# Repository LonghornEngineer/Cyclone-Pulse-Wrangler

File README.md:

Cyclone Pulse Wrangler
========

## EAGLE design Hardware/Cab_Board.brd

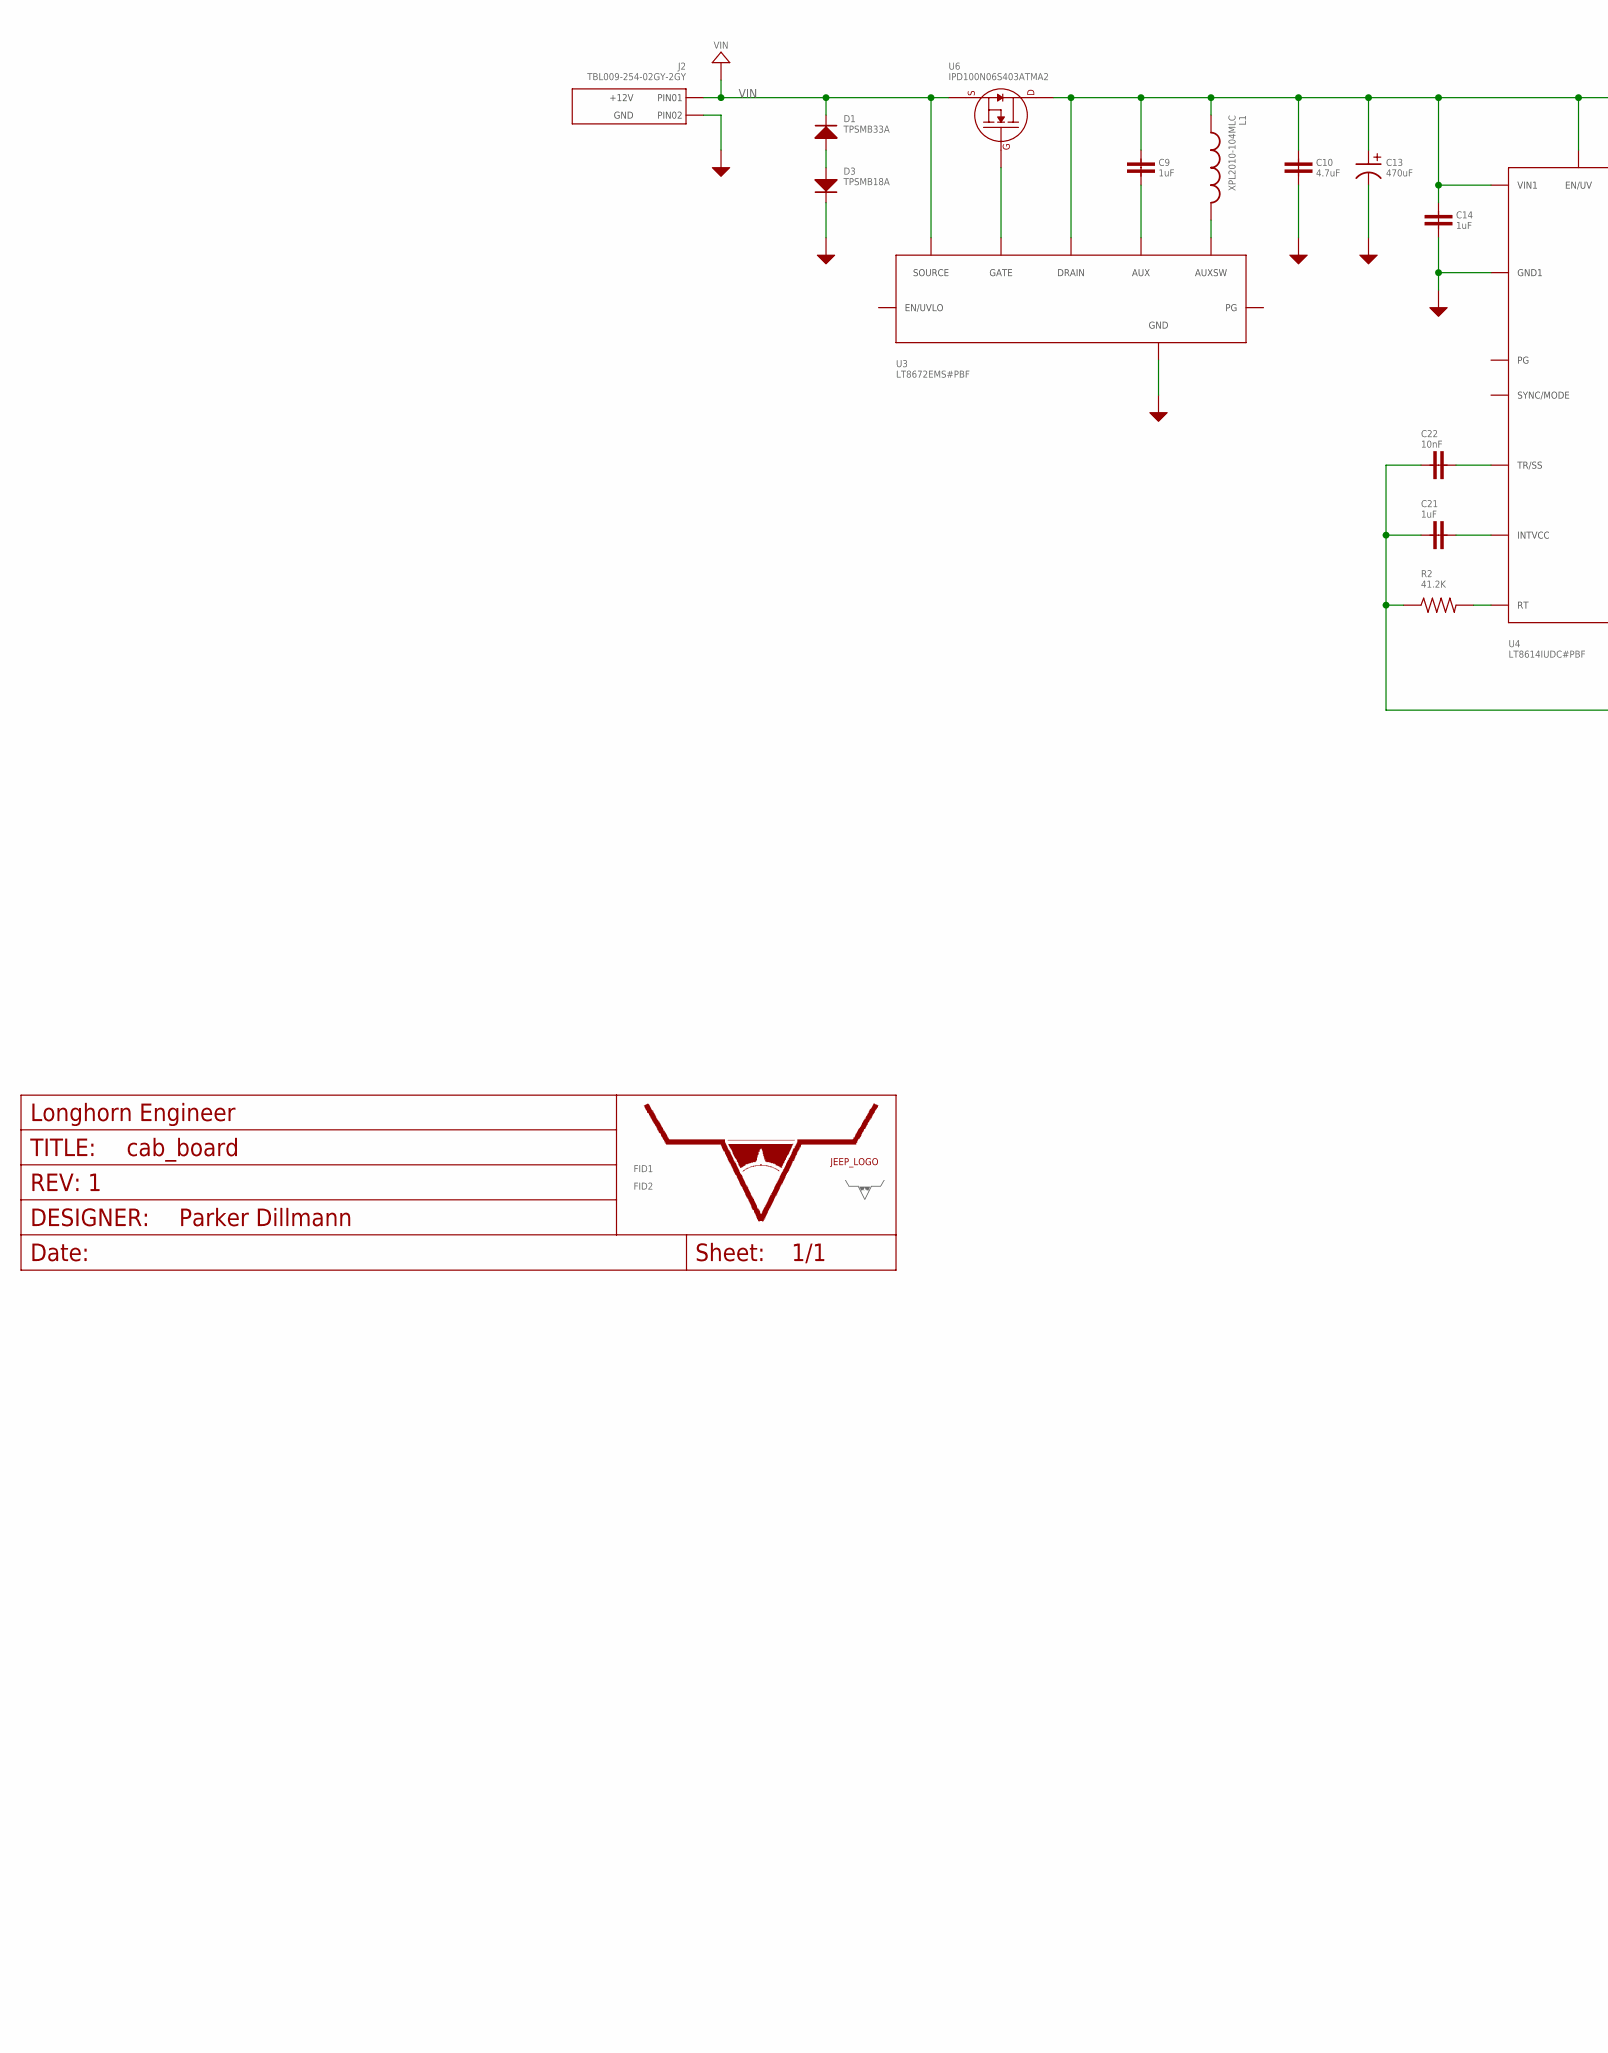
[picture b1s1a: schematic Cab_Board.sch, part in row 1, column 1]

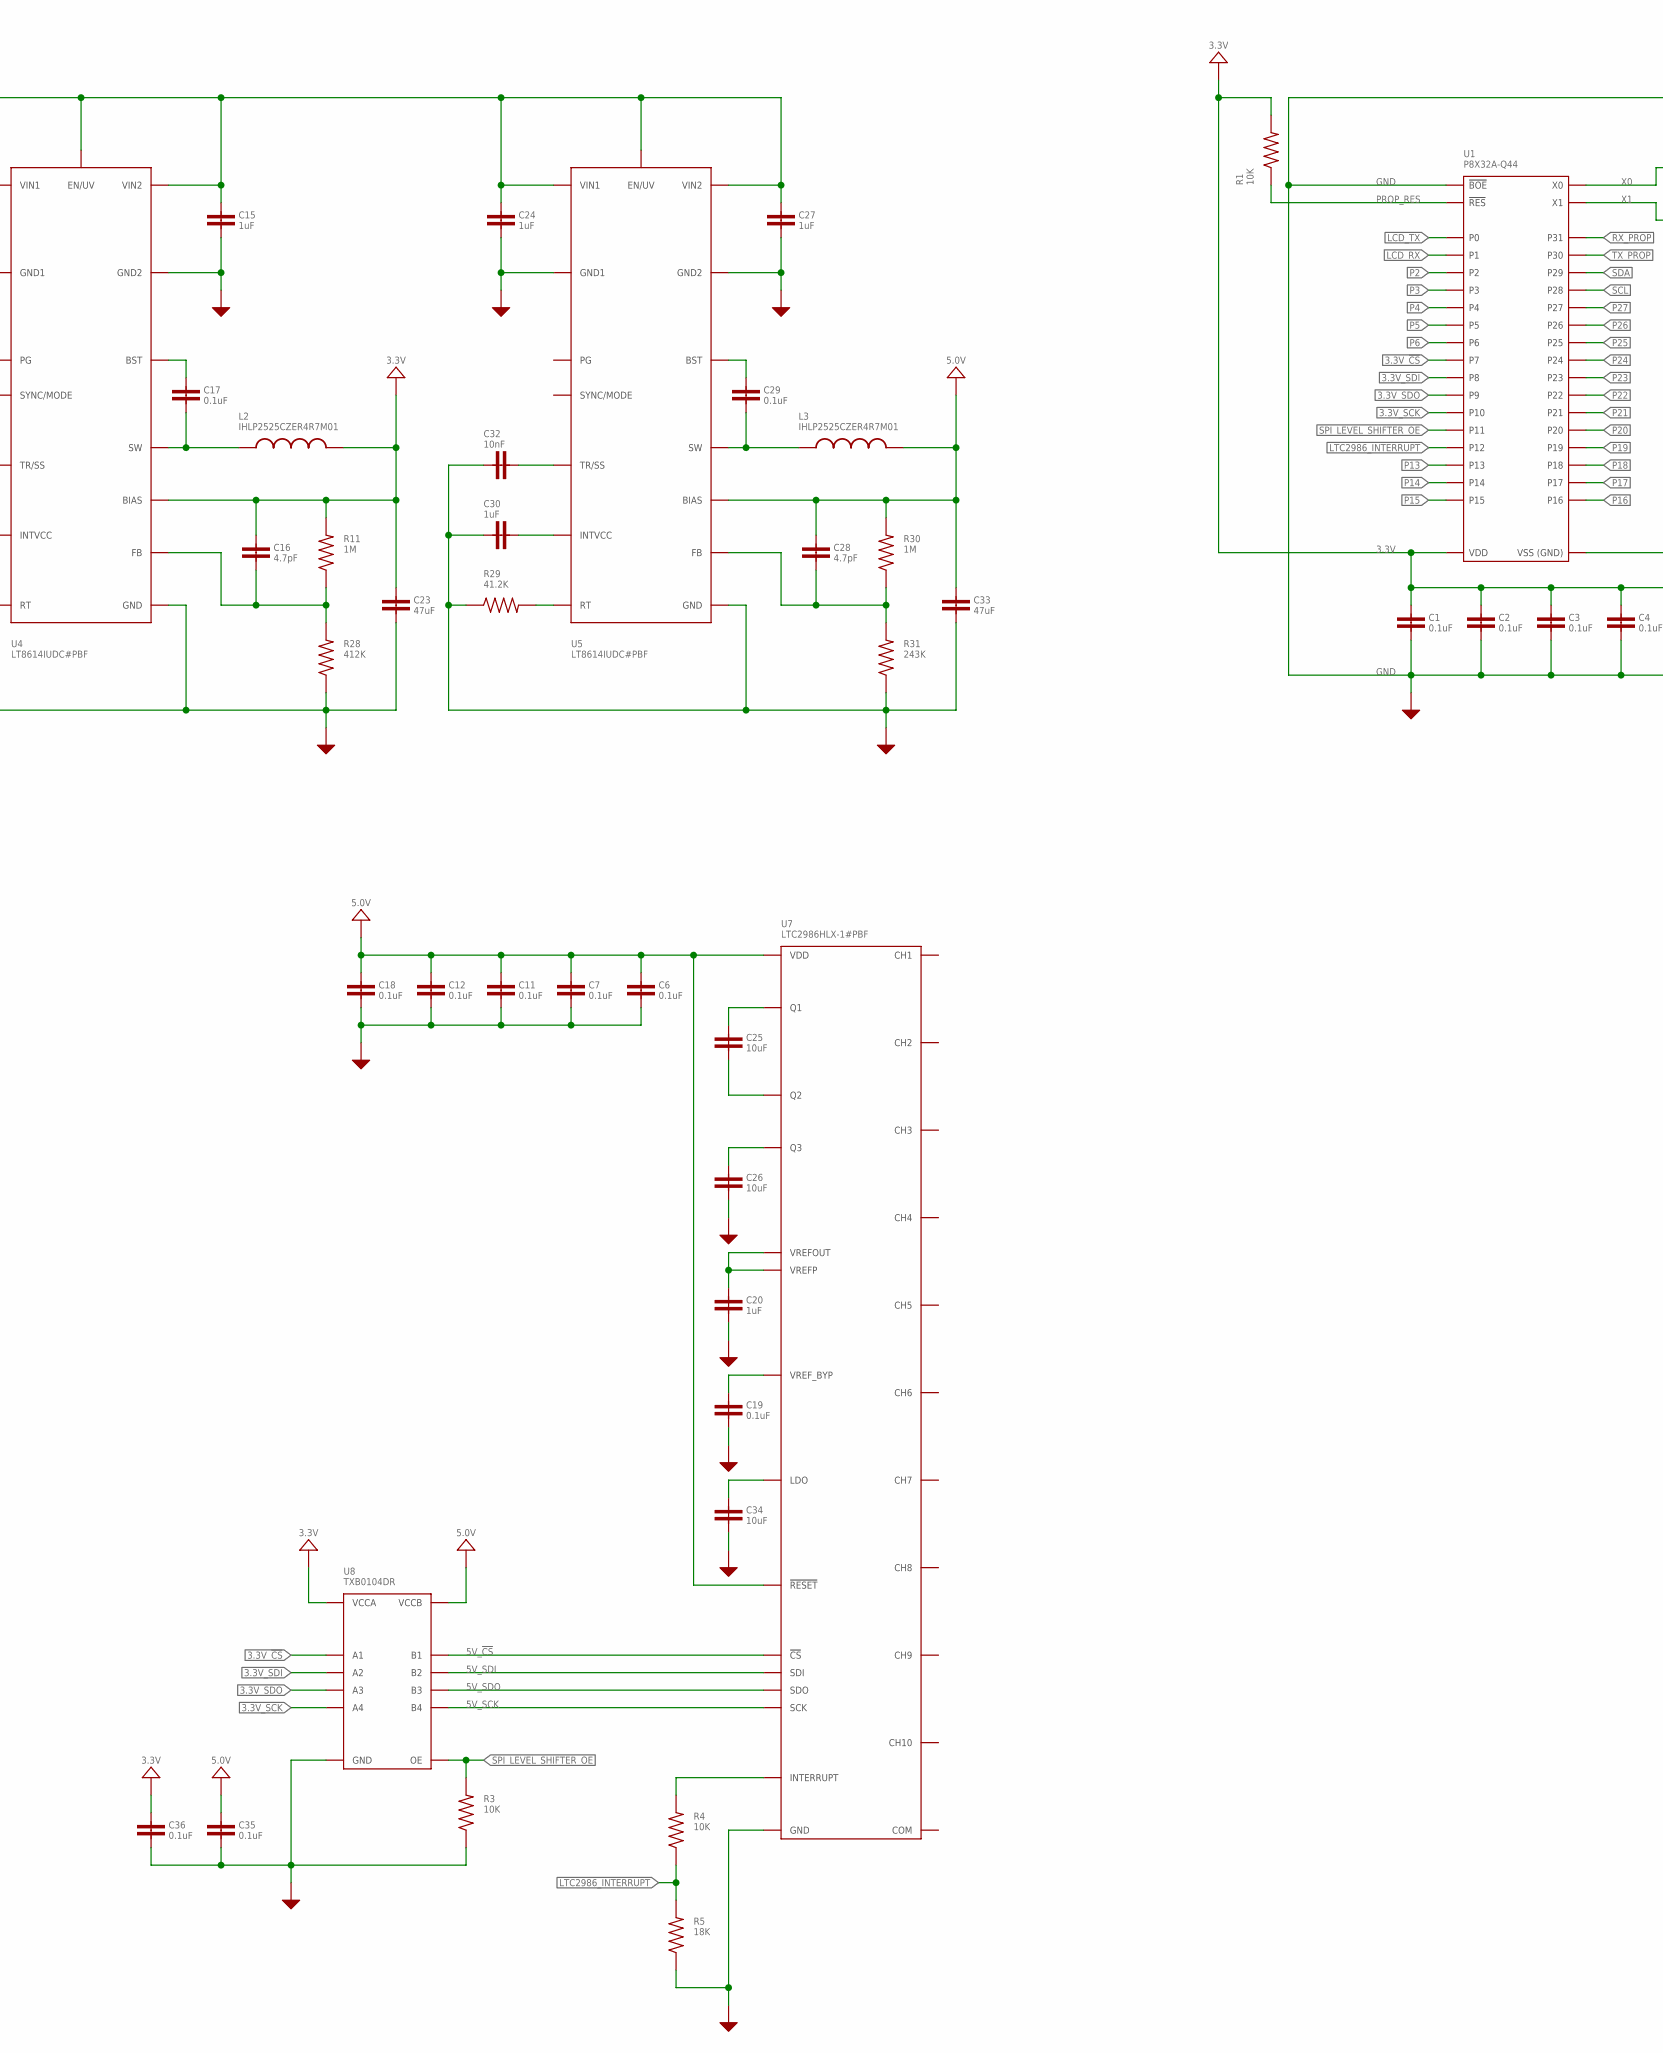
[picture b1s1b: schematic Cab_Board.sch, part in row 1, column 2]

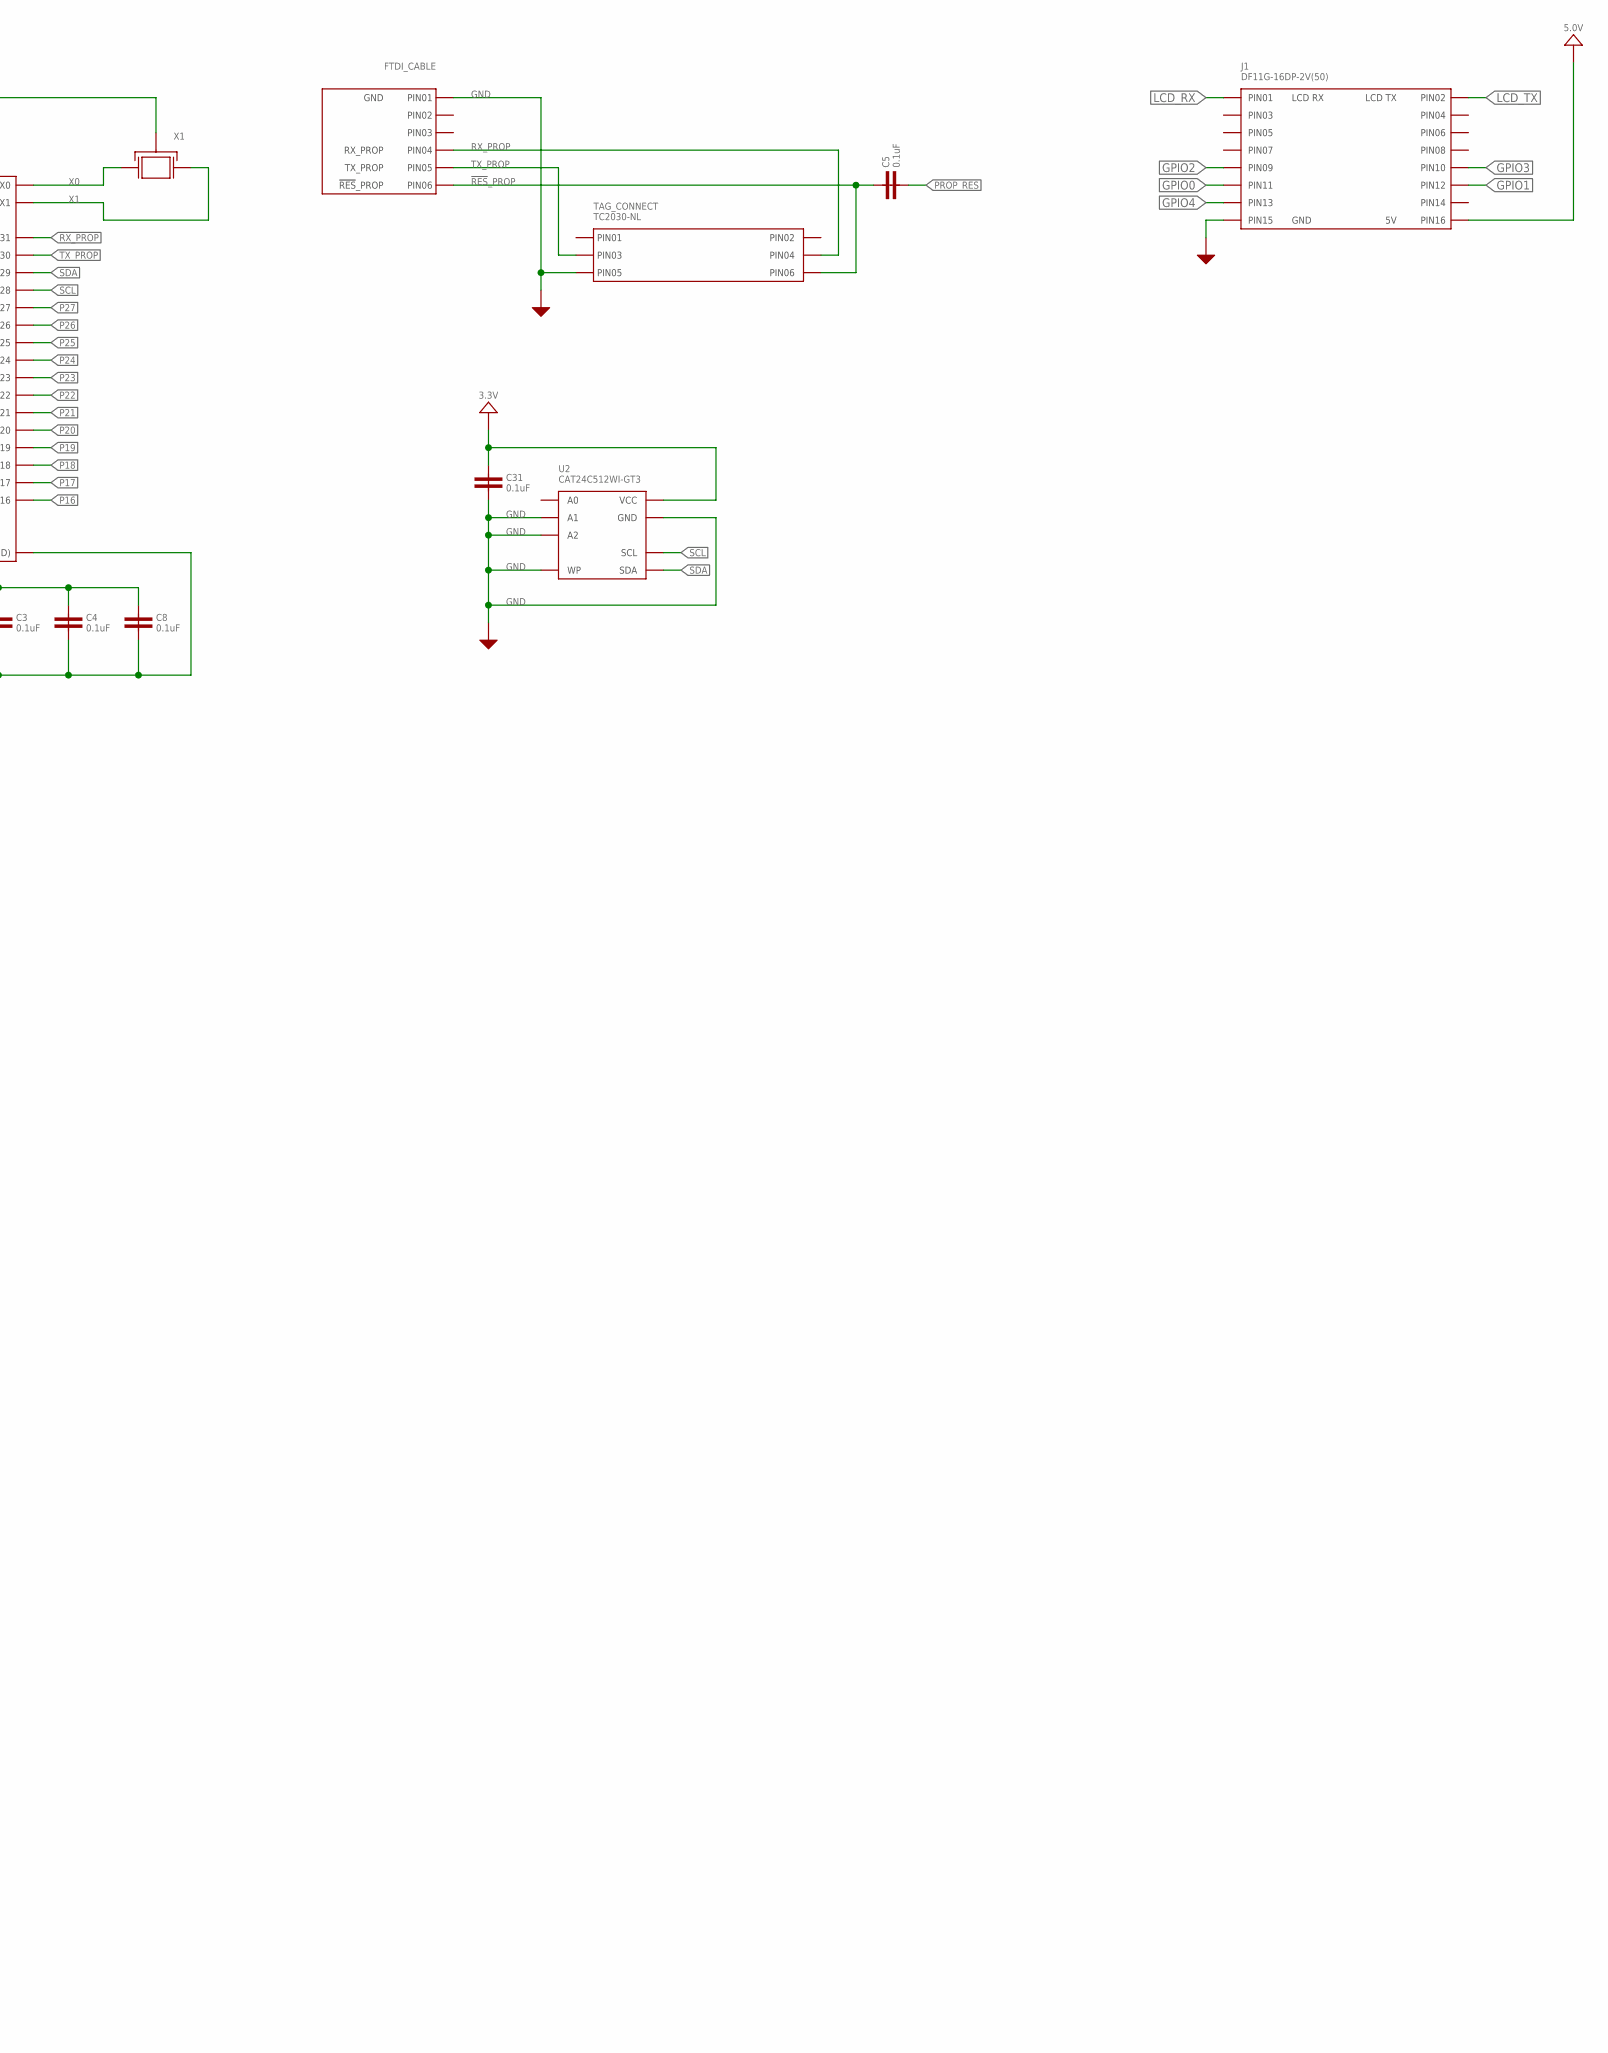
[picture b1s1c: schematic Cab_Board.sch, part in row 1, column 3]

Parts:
C1, C2, C3, C4, C6, C7, C8, C11, C12, C18, C19, C31, C35, C36: 0.1uF; 0805; MPN MF-CAP-0805-0.1uF
C5: 0.1uF; 0603; MPN MF-CAP-0805-0.1uF
C9, C14, C15, C21, C24, C27, C30: 1uF; 0805; MPN C0805X105K5RACAUTO
C10: 4.7uF; 1210; MPN UMJ325AB7475KMHP
C13: 470uF; 10MM_CAP_SMD; MPN EEH-ZS1V471P
C16, C28: 4.7pF; 0603; MPN C0603C479D5HACTU
C17, C29: 0.1uF; 0603; MPN MF-CAP-0603-0.1uF
C20: 1uF; 0805; MPN MF-CAP-0805-1uF
C22, C32: 10nF; 0603; MPN C0603X103K5RAC3316
C23, C33: 47uF; 1210; MPN GCJ32ER70J476KE01L
C25, C26, C34: 10uF; 1210; MPN CGA6P1X7R1N106K250AC
D1: TPSMB33A; DO-214AA; MPN TPSMB33A
D3: TPSMB18A; DO-214AA; MPN TPSMB18A
FID1, FID2: FIDUCIAL_0.5MM
FTDI_CABLE: CON_01X06_2.54MM_PIN_HEADER; 2.54MM_01X06_PIN_HEADER
J1: DF11G-16DP-2V(50); MPN DF11G-16DP-2V(50)
J2: TBL009-254-02GY-2GY
L1: XPL2010-104MLC; XPL2010; MPN XPL2010-104MLC
L2, L3: IHLP2525CZER4R7M01; IHLP-2525; MPN IHLP2525CZER4R7M01
R1: 10K; 0805
R2, R29: 41.2K; 0603
R3, R4: 10K; 0603; MPN MF-RES-0603-10K
R5: 18K; 0603
R11, R30: 1M; 0603
R28: 412K; 0603
R31: 243K; 0603
TAG_CONNECT: TC2030-NL; TC2030
U1: P8X32A-Q44; LQFP44
U2: CAT24C512WI-GT3; SOIC-8_W; MPN CAT24C512WI-GT3
U3: LT8672EMS#PBF; LT8672_MSOP-10; MPN LT8672EMS#PBF
U4, U5: LT8614IUDC#PBF; LT8614_QFN-18; MPN LT8614IUDC#PBF
U6: IPD100N06S403ATMA2; TO-252-3; MPN IPD100N06S403ATMA2
U7: LTC2986HLX-1#PBF; LQFP-48; MPN LTC2986HLX-1#PBF
U8: TXB0104DR; TXB0104_SOIC-14
U$1: LHE_FRAME
U$35: JEEP_LOGO_SILK_MEDIUM; JEEP_SILK_MEDIUM
U$42: LHE_LOGOLHE_LOGO; LHE_LOGO
X1: 6.0MHz; 7MMX5MM; MPN ABMM-6.000MHZ-B2-T

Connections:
3.3V: C1.1, C2.1, C3.1, C4.1, C8.1, C16.1, C23.1, C31.1, C36.1, L2.P$2, R1.2, R11.2, U1.8 (VDD), U1.18 (VDD), U1.30 (VDD), U1.40 (VDD), U2.8 (VCC), U4.1 (BIAS), U8.1 (VCCA)
3.3V_!CS: U1.4 (P7), U8.2 (A1)
3.3V_SCK: U1.11 (P10), U8.5 (A4)
3.3V_SDI: U1.9 (P8), U8.3 (A2)
3.3V_SDO: U1.10 (P9), U8.4 (A3)
5.0V: C6.1, C7.1, C11.1, C12.1, C18.1, C28.1, C33.1, C35.1, J1.P$16 (16), L3.P$2, R30.2, U5.1 (BIAS), U7.P$2 (VDD), U7.P$4 (VDD), U7.P$6 (VDD), U7.P$8 (VDD), U7.P$42 (!RESET), U7.P$45 (VDD), U8.14 (VCCB)
5V_!CS: U7.P$41 (!CS), U8.13 (B1)
5V_SCK: U7.P$38 (SCK), U8.10 (B4)
5V_SDI: U7.P$40 (SDI), U8.12 (B2)
5V_SDO: U7.P$39 (SDO), U8.11 (B3)
!RES!_PROP: C5.1, FTDI_CABLE.6, TAG_CONNECT.P$6 (PIN6)
BST: C17.1, U4.3 (BST)
BST1: C29.1, U5.3 (BST)
FB: C16.2, R11.1, R28.2, U4.20 (FB)
FB1: C28.2, R30.1, R31.2, U5.20 (FB)
GND: C1.2, C2.2, C3.2, C4.2, C6.2, C7.2, C8.2, C10.2, C11.2, C12.2, C13.NEG, C14.2, C15.2, C18.2, C19.2, C20.2, C21.1, C22.1, C23.2, C24.2, C26.2, C27.2, C30.1, C31.2, C32.1, C33.2, C34.2, C35.2, C36.2, D3.C (CATHODE), FTDI_CABLE.1, J1.P$15 (15), J2.2A (PIN2), J2.2B (PIN2), R2.1, R3.1, R5.1, R28.1, R29.1, R31.1, TAG_CONNECT.P$5 (PIN5), U1.5 (VSS), U1.6 (BOE'), U1.17 (VSS), U1.27 (VSS), U1.39 (VSS), U2.2 (A1), U2.3 (A2), U2.4 (GND), U2.7 (WP), U3.2 (GND), U3.4 (GND), U4.6 (GND1), U4.7 (GND1), U4.10 (GND2), U4.11 (GND2), U4.18 (GND), U5.6 (GND1), U5.7 (GND1), U5.10 (GND2), U5.11 (GND2), U5.18 (GND), U7.P$1 (GND), U7.P$3 (GND), U7.P$5 (GND), U7.P$7 (GND), U7.P$9 (GND), U7.P$12 (GND), U7.P$15 (GND), U7.P$26 (GND), U7.P$27 (GND), U7.P$28 (GND), U7.P$29 (GND), U7.P$30 (GND), U7.P$31 (GND), U7.P$32 (GND), U7.P$33 (GND), U7.P$34 (GND), U7.P$35 (GND), U7.P$44 (GND), U8.7 (GND), X1.P$2 (GND), X1.P$4 (GND)
GPIO0: J1.P$11 (11)
GPIO1: J1.P$12 (12)
GPIO2: J1.P$9 (9)
GPIO3: J1.P$10 (10)
GPIO4: J1.P$13 (13)
INTVCC: C21.2, U4.2 (INTVCC)
INTVCC1: C30.2, U5.2 (INTVCC)
LCD_RX: J1.P$1 (1), U1.42 (P1)
LCD_TX: J1.P$2 (2), U1.41 (P0)
LTC2986_INTERRUPT: R4.1, R5.2, U1.13 (P12)
unnamed: C19.1, U7.P$11 (VREF_BYP)
unnamed: U3.10 (GATE), U6.1 (GATE)
unnamed: C20.1, U7.P$13 (VREFOUT), U7.P$14 (VREFP)
unnamed: C26.1, U7.P$46 (Q3)
unnamed: C25.2, U7.P$47 (Q2)
unnamed: C25.1, U7.P$48 (Q1)
unnamed: C34.1, U7.P$43 (LDO)
unnamed: D1.A (ANODE), D3.A (ANODE)
unnamed: R4.2, U7.P$37 (INTERRUPT)
unnamed: C9.1, C10.1, C13.POS, C14.1, C15.1, C24.1, C27.1, L1.P$1, U3.8 (DRAIN), U4.4 (VIN1), U4.13 (VIN2), U4.14 (EN/UV), U5.4 (VIN1), U5.13 (VIN2), U5.14 (EN/UV), U6.PAD (DRAIN)
unnamed: C9.2, U3.7 (AUX)
unnamed: L1.P$2, U3.6 (AUXSW)
P2: U1.43 (P2)
P3: U1.44 (P3)
P4: U1.1 (P4)
P5: U1.2 (P5)
P6: U1.3 (P6)
P13: U1.14 (P13)
P14: U1.15 (P14)
P15: U1.16 (P15)
P16: U1.19 (P16)
P17: U1.20 (P17)
P18: U1.21 (P18)
P19: U1.22 (P19)
P20: U1.23 (P20)
P21: U1.24 (P21)
P22: U1.25 (P22)
P23: U1.26 (P23)
P24: U1.31 (P24)
P25: U1.32 (P25)
P26: U1.33 (P26)
P27: U1.34 (P27)
PROP_RES: C5.2, R1.1, U1.7 (RES')
RT: R2.2, U4.15 (RT)
RT1: R29.2, U5.15 (RT)
RX_PROP: FTDI_CABLE.4, TAG_CONNECT.P$4 (PIN4), U1.38 (P31)
SCL: U1.35 (P28), U2.6 (SCL)
SDA: U1.36 (P29), U2.5 (SDA)
SPI_LEVEL_SHIFTER_OE: R3.2, U1.12 (P11), U8.8 (OE)
SW: C17.2, L2.P$1, U4.8 (SW), U4.9 (SW), U4.21 (SW), U4.22 (SW)
SW1: C29.2, L3.P$1, U5.8 (SW), U5.9 (SW), U5.21 (SW), U5.22 (SW)
TR/SS: C22.2, U4.16 (TR/SS)
TR/SS1: C32.2, U5.16 (TR/SS)
TX_PROP: FTDI_CABLE.5, TAG_CONNECT.P$3 (PIN3), U1.37 (P30)
VIN: D1.C (CATHODE), J2.1A (PIN1), J2.1B (PIN1), U3.9 (SOURCE), U6.3 (SOURCE)
X0: U1.29 (X0), X1.P$3 (X1)
X1: U1.28 (X1), X1.P$1 (X0)

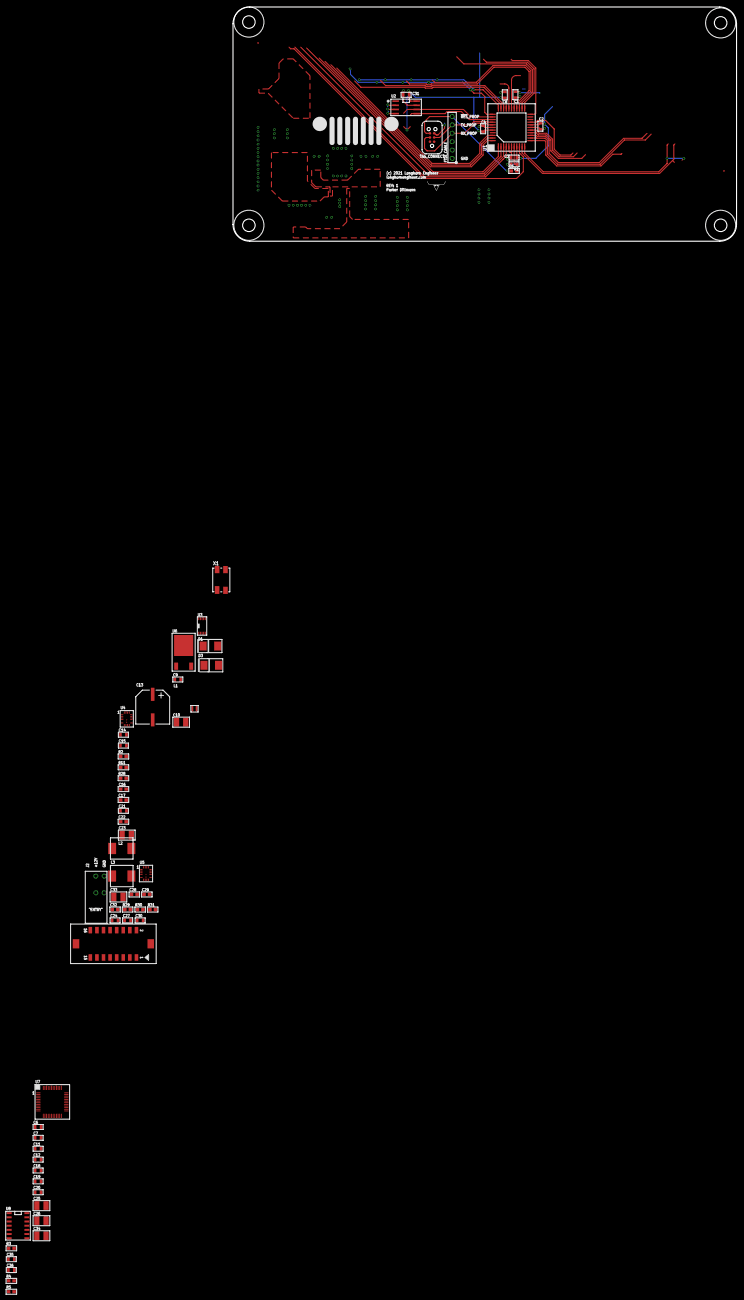
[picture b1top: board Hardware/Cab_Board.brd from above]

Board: 2 copper layers, 152.9 x 71.1 mm, 73 parts (0 on the bottom side), 48 nets.

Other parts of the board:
U$31, U$32, U$33, U$34: MOUNT_HOLE_150MIL

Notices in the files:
parts and their libraries:
PP_Aesthetics: (c) 2016 Longhorn Engineer
PP_Aesthetics: (c) 2021 Longhorn Engineer
